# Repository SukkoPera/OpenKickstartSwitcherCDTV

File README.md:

# OpenKickstartSwitcher CDTV Edition
OpenKickstartSwitcherCDTV is an Open Hardware Kickstart Switcher for the Commodore CDTV.

### Summary
OpenKickstartSwitcherCDTV is a Kickstart switcher for the Commodore CDTV Entertainment System, based on [work by Henryk Richter](http://bax.comlab.uni-rostock.de/en/hardware/amiga500/kickstart-eprom/). It is basically the same circuit/board as [OpenKickstartSwitcher](https://github.com/SukkoPera/OpenKickstartSwitcher) but tailored in shape to the CDTV.

It allows switching among three or six different Kickstart images stored in an EPROM. The switching can be done through physical switches or by pressing the mouse/joystick buttons at power-up. The latter requires [an external add-on board](https://github.com/SukkoPera/OpenAmigaMouseTrigger) that is another project of mine.

### Assembly
Solder all components to the board. Starting with the smaller components might be a good idea, and make sure to solder the pin headers and resistor arrays before the socket. When soldering the resistor arrays, don't push them fully through the holes, as you will need to bend them against the board. No particular order is recommended for the remaining components.

The value of the two single resistors is not critical, 10k is recommended but probably any value between 5k and 50k will do.

My tests show that an SN74HC00 gate works fine. I don't recommend using parts from the *HC* series though, *HCT* or *LS* should be preferred.

The two resistor arrays are not always needed. You might get away without them, depending on the particular EPROM you are using: I have several EPROMs of the same model (but different production batches), and some need the resistors while others don't, so the only way to find out is actual testing. If you decide to install them, they must be of the *bussed* type and the recommended value is 4.7k. Be aware that these parts are polarized and must be installed with the right orientation!

### EPROM Selection and Switch Wiring
The adapter can be used with either 27C800 or 27C160 EPROMs. I recommend using *-100F1* EPROMs by ST, but access time is not critical: use 100ns or faster EPROMs if you can, but anything up to 150ns should work reliably.

#### 27C800
With a 27C800 EPROM, the adapter supports 2x256 KB Kickstart images (i.e.: up to version 1.3) and 1x512 KB image (version 2 and later).

To switch between ROMs, you will need two SPDT switches, connected to the SW1/SW2 pads and ground. A ground pad is available on the board, but any ground spot on the mainboard can be used as well, if easier to reach.

| ROM Image # | Size (KB) | SW1 | SW2 |
|-------------|-----------|-----|-----|
| 1           | 256       | LOW | LOW |
| 2           | 256       | HIGH| LOW |
| 3           | 512       |  x  | HIGH|

(x = Don't Care)

So, basically:
* If SW2 is HIGH, the 512 KB Kickstart image is selected, regardless of SW1.
* If SW2 is LOW, SW1 controls which one of the two 256 KB images is enabled: LOW selects the first one, and HIGH selects the second one.

You can also use a single ON-OFF-ON DPDT switch, just wire ground to the middle pins, SW1 and SW2 on one side and SW2 on the other.

As SW1/SW2 will both read as HIGH if left unconnected, the 512 KB Kickstart will be selected if no switches are wired.

You can fully ignore the A19 pad on the bottom side of the board, when using a 27C800 EPROM.

#### 27C160
With a 27C160 EPROM, the adapter supports up to 4x256 KB Kickstart images and 2x512 KB images.

You will need to solder an additional switch to the A19 pad on the bottom side of the board. VCC and GND pads are provided nearby so that you can also solder a pull-up/down resistor.

| ROM Image # | Size (KB) | SW1 | SW2 | A19 |
|-------------|-----------|-----|-----|-----|
| 1           | 256       | LOW | LOW | LOW |
| 2           | 256       | HIGH| LOW | LOW |
| 3           | 512       |  x  | HIGH| LOW |
| 4           | 256       | LOW | LOW | HIGH|
| 5           | 256       | HIGH| LOW | HIGH|
| 6           | 512       |  x  | HIGH| HIGH|

**IMPORTANT: ALWAYS TURN YOUR CDTV OFF BEFORE MOVING THE SELECTION SWITCHES.**

#### Flashing Notes
When flashing the EPROM, make sure that the ROM images you are using are exactly 262144 or 524288 bytes long, and just concatenate them. Take care to use the correct byte ordering, as the Amiga hardware expects 16-bit words to be stored in the *big-endian* format (which is NOT the format UAE expects them in, for the record). On Unix-like systems you can use the *conv=swab* option of *dd* to change the byte ordering.

27C800s and 27C160 are 42-pin EPROMs and most programmers only support chips up to 40 pins. This is the case with [the popular TL866 programmer](http://autoelectric.cn/EN/TL866_main.html), for instance. You can get around this limitation with an adapter PCB. There are at least two open designs of such an adapter:
* [One by keirff](https://github.com/keirf/PCB-Projects) (who, interestingly, has his own Kickstart Switcher)
* [And another one by gaggi](https://github.com/gaggi/27c160-tl866-adapter)

I have only used the latter and found it to be working fine.

### Installation
Once your OpenKickstartSwitcherCDTV is assembled and programmed, the rest of the installation should be pretty straightforward:
* Open your CDTV.
* Identify the Kickstart chip.
* Carefully remove it.
* Plug OpenKickstartSwitcher in its place, making sure to match the correct orientation.
* Drill some holes into the back of your CDTV (or wherever you prefer) and screw some switches in there.
* Solder wires to switches.
* Close your CDTV.

Of course, if you use OpenAmigaMouseTrigger there is no need to drill any holes.

### DiagROM
The excellent [DiagROM by chucky](http://www.diagrom.com) can be used with OpenKickstartSwitcherCDTV, even though not all functions work on a CDTV.

Normally it is distributed as a 512 KB image, but most of the space is unused, so I have created a 256 KB version of DiagROM 1.0 by simply truncating the image. It is **NOT GUARANTEED TO WORK**, but it looks fine to me. It can be [downloaded here](https://github.com/SukkoPera/OpenKickstartSwitcher/files/1777856/diagrom-256k.zip).

### License
The OpenKickstartSwitcherCDTV documentation, including the design itself, is copyright &copy; SukkoPera 2018-2019.

OpenKickstartSwitcherCDTV is Open Hardware licensed under the [CERN OHL v. 1.2](http://ohwr.org/cernohl).

You may redistribute and modify this documentation under the terms of the CERN OHL v.1.2. This documentation is distributed *as is* and WITHOUT ANY EXPRESS OR IMPLIED WARRANTIES whatsoever with respect to its functionality, operability or use, including, without limitation, any implied warranties OF MERCHANTABILITY, SATISFACTORY QUALITY, FITNESS FOR A PARTICULAR PURPOSE or infringement. We expressly disclaim any liability whatsoever for any direct, indirect, consequential, incidental or special damages, including, without limitation, lost revenues, lost profits, losses resulting from business interruption or loss of data, regardless of the form of action or legal theory under which the liability may be asserted, even if advised of the possibility or likelihood of such damages.

A copy of the full license is included in file [LICENSE.pdf](LICENSE.pdf), please refer to it for applicable conditions. In order to properly deal with its terms, please see file [LICENSE_HOWTO.pdf](LICENSE_HOWTO.pdf).

The contact points for information about manufactured Products (see section 4.2) are listed in file [PRODUCT.md](PRODUCT.md).

Any modifications made by Licensees (see section 3.4.b) shall be recorded in file [CHANGES.md](CHANGES.md).

The Documentation Location of the original project is https://github.com/SukkoPera/OpenKickstartSwitcherCDTV/.

### Support the Project
Since the project is open you are free to get the PCBs made by your preferred manufacturer, however in case you want to support the development, you can order them from PCBWay through this link:

You get cheap, professionally-made and good quality PCBs, I get some credit that will help with this and [other projects](https://www.pcbway.com/project/member/shareproject/?bmbid=41100). You won't even have to worry about the various PCB options, it's all pre-configured for you!

Also, if you still have to register to that site, [you can use this link](https://www.pcbway.com/setinvite.aspx?inviteid=41100) to get some bonus initial credit (and yield me some more).

Again, if you want to use another manufacturer, feel free to, don't feel obligated :). But then you can buy me a coffee if you want:

### Get Help
If you need help or have questions, you can join [the official Telegram group](https://t.me/joinchat/HUHdWBC9J9JnYIrvTYfZmg).

### Thanks
Thanks to Henryk Richter, Aldo PRS and [screwbreaker](https://github.com/screwbreaker).

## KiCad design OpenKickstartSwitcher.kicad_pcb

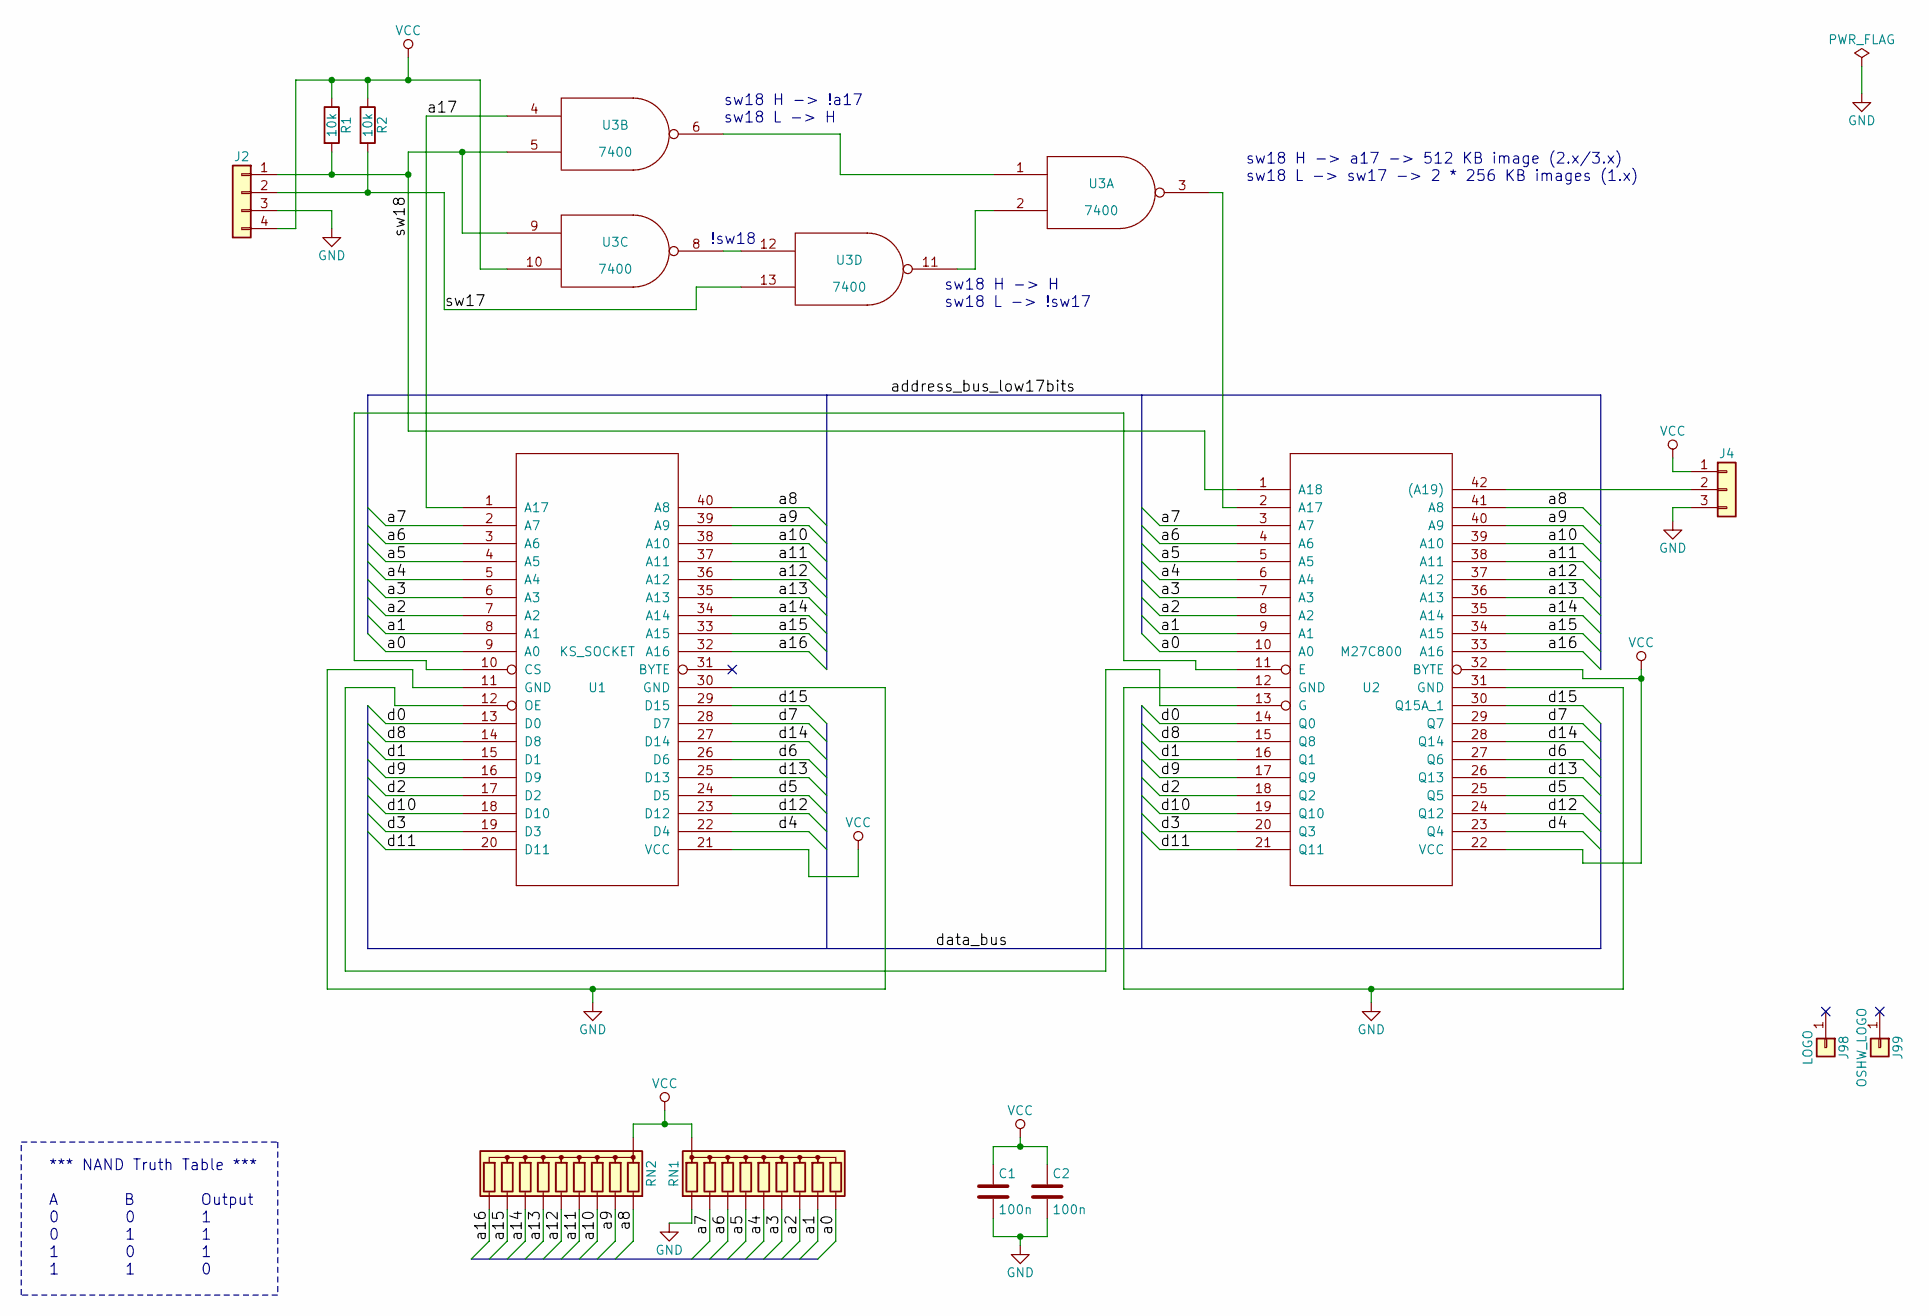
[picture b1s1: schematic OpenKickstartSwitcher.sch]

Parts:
C1, C2: 100n; C_Disc_D7.0mm_W2.5mm_P5.00mm
J2: Conn_01x04; Solderable_PinHeader_1x04
J4: Conn_01x03; SolderJumper
J98: LOGO; logo
J99: OSHW_LOGO; Logo_copper_OSHW_6x6mm
R1, R2: 10k; R_Axial_DIN0204_L3.6mm_D1.6mm_P7.62mm_Horizontal
RN1, RN2: 4.7k; R_Array_SIP10_OnSide
U1: KS_SOCKET; DIP-40_DualHeaderStrips
U2: M27C800; DIP-42_Socket
U3: 7400; DIP-14_W7.62mm_Socket

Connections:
/a0: RN1.10 (R9), U1.9 (A0), U2.10 (A0)
/a1: RN1.9 (R8), U1.8 (A1), U2.9 (A1)
/a2: RN1.8 (R7), U1.7 (A2), U2.8 (A2)
/a3: RN1.7 (R6), U1.6 (A3), U2.7 (A3)
/a4: RN1.6 (R5), U1.5 (A4), U2.6 (A4)
/a5: RN1.5 (R4), U1.4 (A5), U2.5 (A5)
/a6: RN1.4 (R3), U1.3 (A6), U2.4 (A6)
/a7: RN1.3 (R2), U1.2 (A7), U2.3 (A7)
/a8: RN2.2 (R1), U1.40 (A8), U2.41 (A8)
/a9: RN2.3 (R2), U1.39 (A9), U2.40 (A9)
/a10: RN2.4 (R3), U1.38 (A10), U2.39 (A10)
/a11: RN2.5 (R4), U1.37 (A11), U2.38 (A11)
/a12: RN2.6 (R5), U1.36 (A12), U2.37 (A12)
/a13: RN2.7 (R6), U1.35 (A13), U2.36 (A13)
/a14: RN2.8 (R7), U1.34 (A14), U2.35 (A14)
/a15: RN2.9 (R8), U1.33 (A15), U2.34 (A15)
/a16: RN2.10 (R9), U1.32 (A16), U2.33 (A16)
/a17: U1.1 (A17), U3.4
/d0: U1.13 (D0), U2.14 (Q0)
/d1: U1.15 (D1), U2.16 (Q1)
/d2: U1.17 (D2), U2.18 (Q2)
/d3: U1.19 (D3), U2.20 (Q3)
/d4: U1.22 (D4), U2.23 (Q4)
/d5: U1.24 (D5), U2.25 (Q5)
/d6: U1.26 (D6), U2.27 (Q6)
/d7: U1.28 (D7), U2.29 (Q7)
/d8: U1.14 (D8), U2.15 (Q8)
/d9: U1.16 (D9), U2.17 (Q9)
/d10: U1.18 (D10), U2.19 (Q10)
/d11: U1.20 (D11), U2.21 (Q11)
/d12: U1.23 (D12), U2.24 (Q12)
/d13: U1.25 (D13), U2.26 (Q13)
/d14: U1.27 (D14), U2.28 (Q14)
/d15: U1.29 (D15), U2.30 (Q15A_1)
/sw17: J2.2, R2.2, U3.13
/sw18: J2.1, R1.2, U2.1 (A18), U3.5, U3.9
GND: C1.2, C2.2, J2.3, J4.3, RN1.2 (R1), U1.11 (GND), U1.30 (GND), U2.12 (GND), U2.31 (GND), U3.7 (GND)
unnamed: J4.2, U2.42 ((A19))
unnamed: U1.10 (CS), U2.11 (E)
unnamed: U1.12 (OE), U2.13 (G)
unnamed: U2.2 (A17), U3.3
unnamed: U3.1, U3.6
unnamed: U3.2, U3.11
unnamed: U3.8, U3.12
VCC: C1.1, C2.1, J2.4, J4.1, R1.1, R2.1, RN1.1 (common), RN2.1 (common), U1.21 (VCC), U2.22 (VCC), U2.32 (BYTE), U3.10, U3.14 (VCC)

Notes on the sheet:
sw18 H -> a17 -> 512 KB image (2.x/3.x) sw18 L -> sw17 -> 2 * 256 KB images (1.x)
!sw18
sw18 H -> !a17 sw18 L -> H
sw18 H -> H sw18 L -> !sw17
*** NAND Truth Table *** A B Output 0 0 1 0 1 1 1 0 1 1 1 0

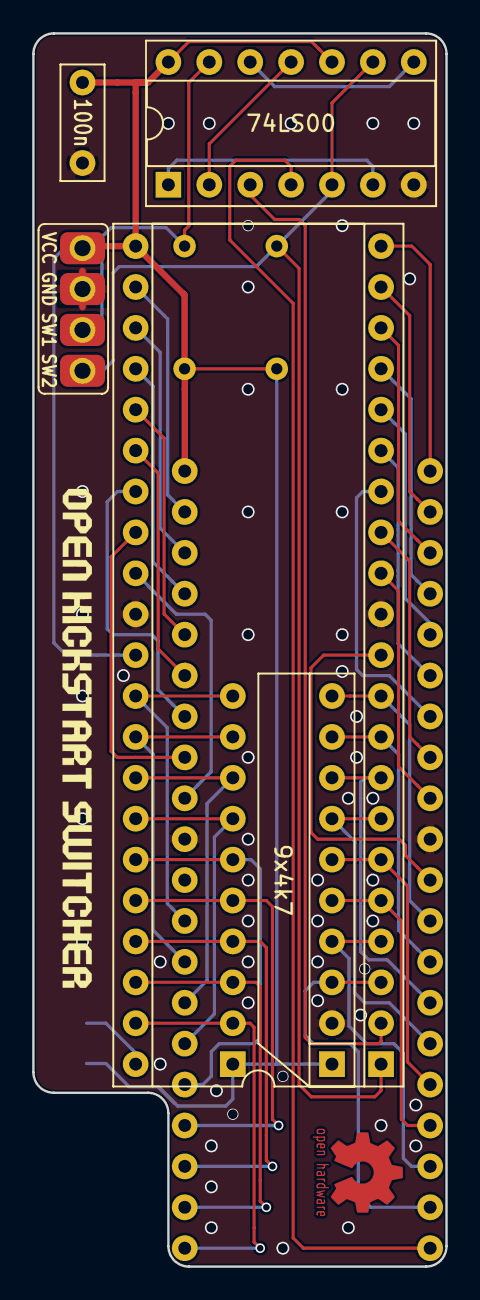
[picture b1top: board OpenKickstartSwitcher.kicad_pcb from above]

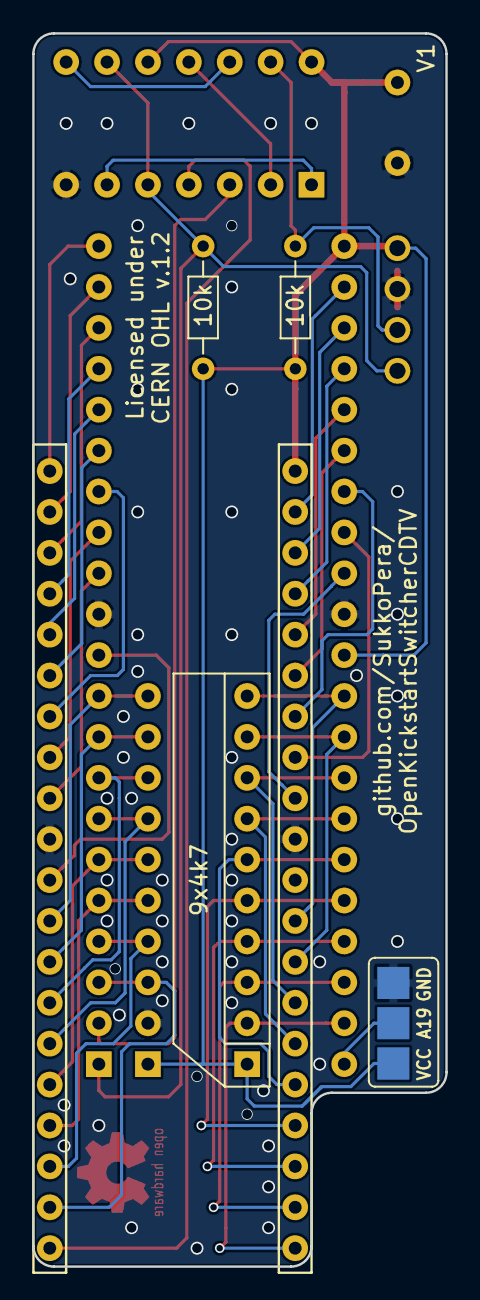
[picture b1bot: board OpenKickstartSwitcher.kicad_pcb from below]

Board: 2 copper layers, 25.7 x 76.6 mm, 12 parts (4 on the bottom side), 45 nets.

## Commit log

2019-02-10 Remove revision jumper and other cosmetic fixes
2019-02-10 Add license & Co.
2019-08-29 Add coffee
